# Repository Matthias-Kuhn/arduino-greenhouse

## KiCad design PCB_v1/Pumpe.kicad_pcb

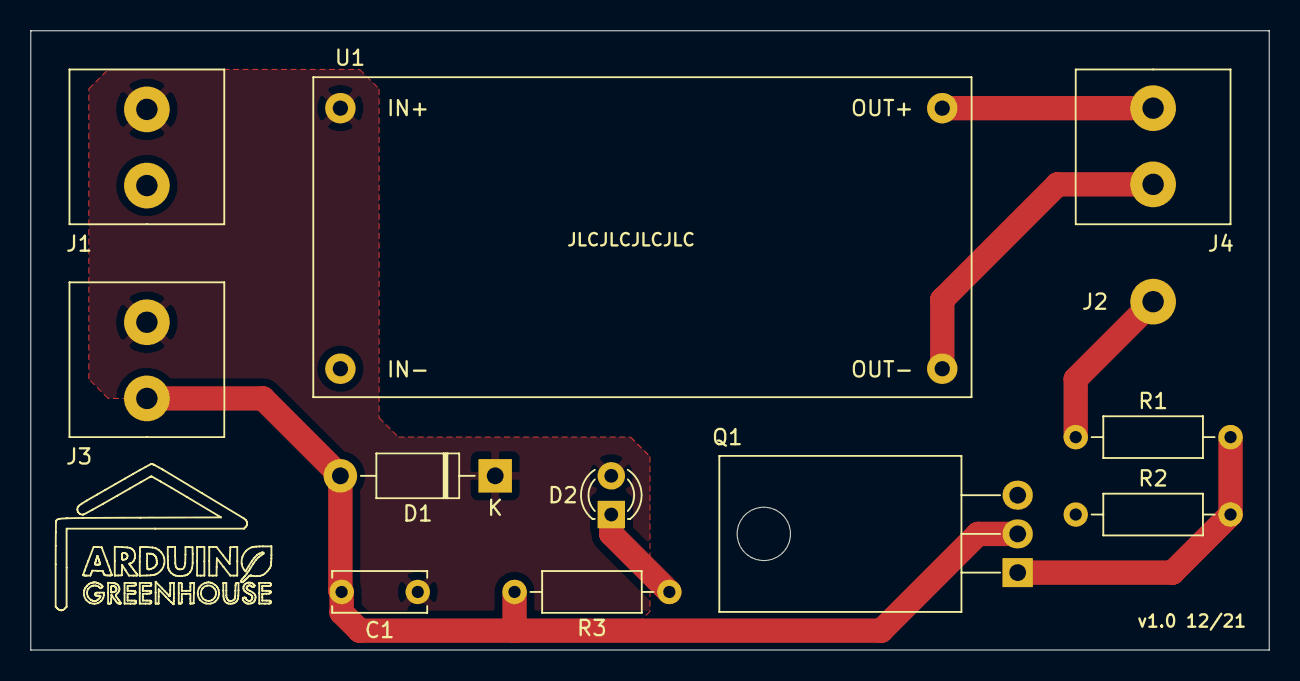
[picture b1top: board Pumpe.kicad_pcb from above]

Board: 2 copper layers, 81.3 x 40.6 mm, 12 parts (0 on the bottom side), 8 nets.

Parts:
C1: 10nF; C_Disc_D6.0mm_W2.5mm_P5.00mm
D1: D; D_DO-41_SOD81_P10.16mm_Horizontal
D2: LED; LED_D3.0mm
J1, J3, J4: Conn_01x02_Female; ConnectorRM5
J2: Conn_01x01_Female; Conncetor1
Q1: TIP120; TO-220-3_Horizontal_TabDown
R1: 200; R_Axial_DIN0207_L6.3mm_D2.5mm_P10.16mm_Horizontal
R2: 100k; R_Axial_DIN0207_L6.3mm_D2.5mm_P10.16mm_Horizontal
R3: 600; R_Axial_DIN0207_L6.3mm_D2.5mm_P10.16mm_Horizontal
U1: LM2596; LM2596PCB

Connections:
+12V: C1.1, D1.1, D2.2, J1.2, J3.2, U1.1
GND: J1.1, Q1.3, R2.1, U1.2
unnamed: C1.2, D1.2, J3.1, Q1.2, R3.2
unnamed: D2.1, R3.1
unnamed: J2.1, R1.1
unnamed: J4.1, U1.3
unnamed: J4.2, U1.4
unnamed: Q1.1, R1.2, R2.2

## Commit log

2021-11-21 implemented watering system
2021-11-21 implemented moisture sensor
2021-11-21 code cleanup
2021-11-22 added dht sensor
2021-11-22 added moisture percentage
2021-12-30 added status display class
2021-12-30 added logo
2021-12-30 added pcb files
2022-04-16 fixed status display bug
2022-04-16 all systems working v1
2022-04-19 implemented bluetooth get/set
